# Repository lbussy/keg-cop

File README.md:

# Keg Cop

*Beverage Lines, Monitored.*

Keg Cop is an inexpensive and, most of all, simple to operate WiFi-enabled solution to maintain information about your Keezer, Kegerator, and Kegs.  Keg Cop enables you to use flowmeters of your choice (Swissflow during development) to monitor the contents of your kegs, and it even has a built-in Web UI to display what is on tap and how much is left.

Keg Cop uses an inexpensive ESP32 controller to control and monitor all aspects of your beverage dispensing solution.  If you already have flowmeters from another project, you can easily use those and upgrade your approach.  It will support one to nine flowmeters, and it will even control your temperatures for you.

You may employ up to five different temperature sensors to show you things like tower temp, keg temp, top and bottom of your Keezer, and you can even monitor the room temperature.

I designed this project as a complete system from the ground up.  Everything is provided, including board files for PCBs and 3D models for cases.  I’m releasing this system as something which provides either a complete recipe for success or enough information to allow you to roll your own if that’s your thing.

Whether you have one flowmeter or nine, Keg Cop can handle them.  Have more?  Add another controller, and KegScreen (coming soon!) will seamlessly display them all.

Want even more capabilities?  Keg Cop will report pours to Raspberry Pints via MQTT or a web endpoint with a generic JSON packet.
Still not enough?  Keg Cop was designed alongside KegScreen to work hand in hand with this exciting upcoming full-featured tap list solution.

Full documentation is provided, including the API and hardware assembly.  Or, if you are a more nuts and bolts person, GitHub may be the place for you!

Links and Support:

-	Home Page
-	Project on GitHub
-	Documentation
-	Report an Issue or Bug
-	Get support or chat with other users

This release has been a long time coming, and I’m excited to share this with you.  I want to thank the following folks from Homebrewtalk who have contributed in one way or another:

-	@thorrak
-	@gromitdj
-	@UncleD
-	@day_trippr
-	@cripplecreek

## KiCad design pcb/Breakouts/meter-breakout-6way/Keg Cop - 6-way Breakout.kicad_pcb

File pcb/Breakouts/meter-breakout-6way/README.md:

# Six-way Meter Breakout PCB

This PCB interfaces between the main Keg Cop board and up to six flow meters, which will connect via board-mounted JST-XH connectors.  This PCB is not designed to daisy-chain.

## Design info
This PCB was designed using [KiCad 6.0](https://www.kicad.org/), a free and open-source, cross-platform electronics design suite.  Design files are provided if you'd like to make changes to the design.  Otherwise, you can download the .zip file from the `Gerber` directory and upload to your PCB fab of choice.

## Board images
Front:

Back:

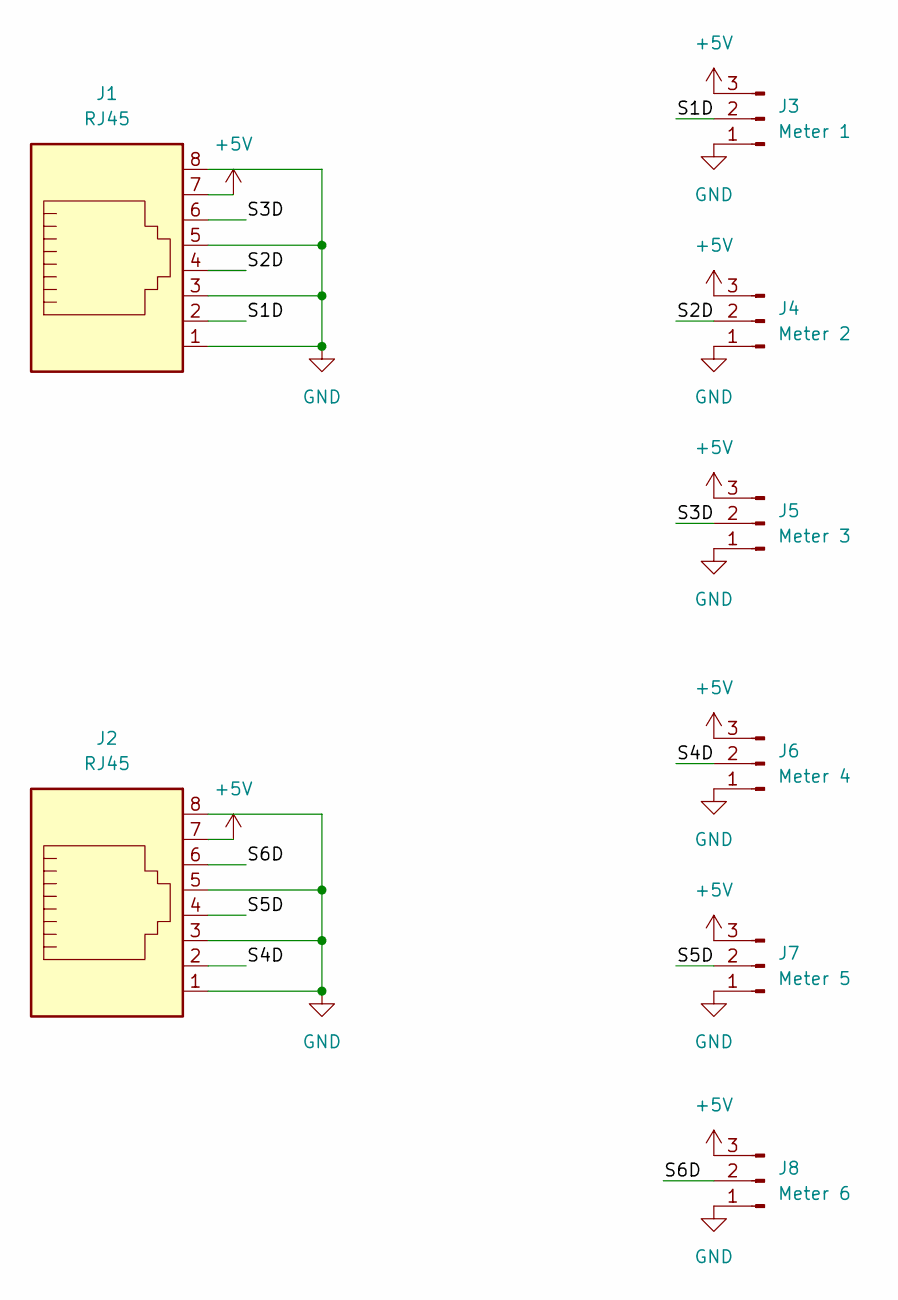
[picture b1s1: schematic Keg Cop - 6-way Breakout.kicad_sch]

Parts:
J1, J2: RJ45; RJ45_Amphenol_54602-x08_Horizontal
J3: Meter 1; JST_XH_B3B-XH-A_1x03_P2.50mm_Vertical
J4: Meter 2; JST_XH_B3B-XH-A_1x03_P2.50mm_Vertical
J5: Meter 3; JST_XH_B3B-XH-A_1x03_P2.50mm_Vertical
J6: Meter 4; JST_XH_B3B-XH-A_1x03_P2.50mm_Vertical
J7: Meter 5; JST_XH_B3B-XH-A_1x03_P2.50mm_Vertical
J8: Meter 6; JST_XH_B3B-XH-A_1x03_P2.50mm_Vertical

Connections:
+5V: J1.7, J2.7, J3.3, J4.3, J5.3, J6.3, J7.3, J8.3
/S1D: J1.2, J3.2
/S2D: J1.4, J4.2
/S3D: J1.6, J5.2
/S4D: J2.2, J6.2
/S5D: J2.4, J7.2
/S6D: J2.6, J8.2
GND: J1.1, J1.3, J1.5, J1.8, J2.1, J2.3, J2.5, J2.8, J3.1, J4.1, J5.1, J6.1, J7.1, J8.1

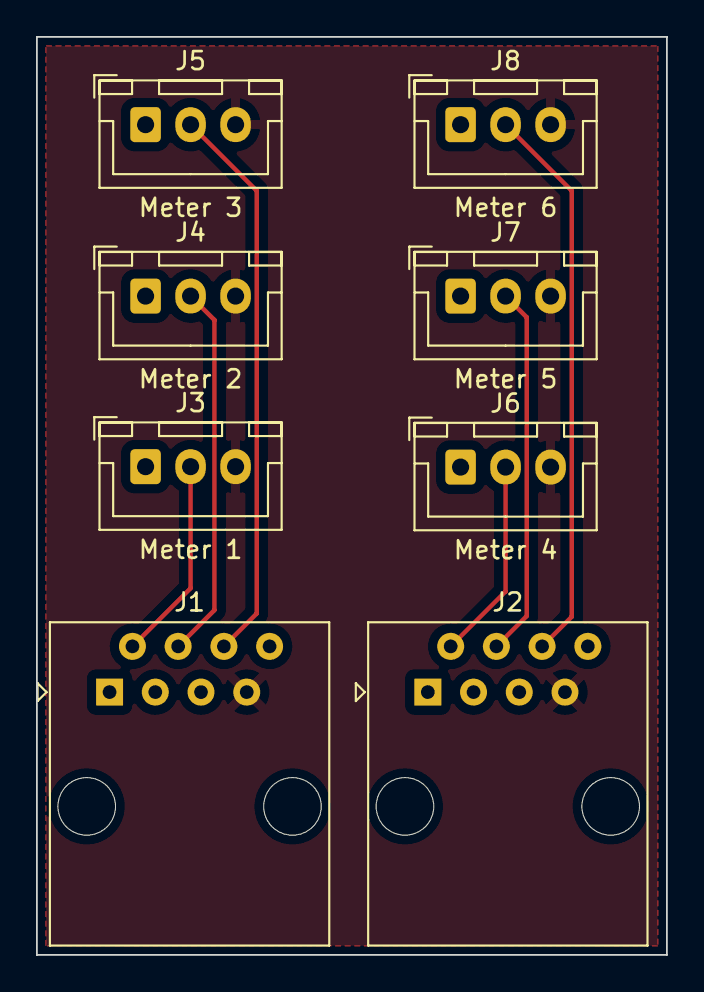
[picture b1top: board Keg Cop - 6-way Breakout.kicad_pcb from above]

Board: 2 copper layers, 35.0 x 51.0 mm, 8 parts (0 on the bottom side), 8 nets.

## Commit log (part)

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2022-09-05 Move JSON to stack
2022-09-05 Cleanup strings
2022-09-06 Move back to dynamic type
2022-09-07 Move common function to common file
2022-09-07 Allow builds outside of a repo
2022-09-07 Refactor API
2022-09-08 Add semaphores to prevent windup
2022-09-09 Use SPIFFS Editor
2022-09-09 Finish vestigial file management
2022-09-09 Fix API docs
2022-09-09 Fix API docs (#132)
2022-09-09 Move secret to a header (#133)
2022-09-09 Fix alert bars
2022-09-09 Fix alert bars (#134)
2022-09-09 Enable menu change on sensor change (#135)
2022-09-09 Version bump
2022-09-12 Update KSTV keys
2022-09-12 Remove debug condition on Telnet
2022-09-12 Cleanup debug (#136)
    * Add kstv.json
    * Update KSTV keys
    * Remove debug condition on Telnet
    * Remove debug condition on /edit
2022-09-12 Make keys public, add functions for KS-TV
2022-09-12 Remove needless keys, move KS-TV
2022-09-12 Fix a couple mistakes
2022-09-12 Kstv json (#137)
    * Add kstv.json
    * Update KSTV keys
    * Cleanup debug (#136)
    * Add kstv.json
    * Update KSTV keys
    * Remove debug condition on Telnet
2022-09-12 Don't need string
2022-09-12 Don't need string (#138)
2022-09-18 Move semaphore earlier
2022-09-18 Move reconnect out of callback
2022-09-18 Filesystem stability (#139)
    * Don't need string
    * Change to 5.0 class for SR-only
    * Move semaphore earlier
    * Move reconnect out of callback
    * Clean up filesystem logic
2022-09-18 Filesystem stability (#140)
    * Don't need string
    * Change to 5.0 class for SR-only
    * Move semaphore earlier
    * Move reconnect out of callback
    * Clean up filesystem logic
2022-09-18 Hide page when theme changes (#141)
2022-09-18 Update TODO
2022-09-21 Version update (#142)
2022-09-23 Remove kegscreen service advertisement
2022-09-25 Fix for #146
2023-04-07 Use proper div
2023-04-09 Go back to platform package 1.0.6
2023-04-11 Stub this in for later
2023-04-11 Explicit python decl
2023-04-11 Add .gz handler
2023-04-11 Update uptime refresh
2023-04-12 Ignore data
2023-04-12 I guess I don't need this
2023-04-12 Fix active links
2023-04-12 Fix fan control enabled assignment
2023-04-12 Fix for #152
2023-04-12 Fix for #149
2023-04-13 Version increment
2023-04-14 Restructure reconnect
2023-04-14 Restart serial and telnet
2023-04-14 Restart Web Server
2023-04-14 Reset main loop and filesystem
2023-04-14 Cleanup
2023-04-15 Cleanup logging
2023-04-15 Add some delays to allow Serial to start
2023-04-15 Lockout
2023-04-15 Separate stop and start
2023-04-15 Fix prefixes
2023-04-15 Loop logic
2023-04-15 Set autoconnect off
2023-04-15 Update Bootswatch
2023-04-15 Stub in hourly reboots
2023-04-15 Dis/reconnect on iter
2023-04-16 Reboot every 1 hour to avoid panic
2023-04-16 Logging cleanup
2023-04-16 Change to 2 hour reboot
2023-04-16 Standardize logic
2023-04-16 Tag new alpha
2023-04-18 Close FS after use
2023-04-19 Use single open/close
2023-04-19 Add delay to see startup Serial
2023-04-21 Fix John's 'feature'
2023-04-21 Refactor return
2023-04-22 Move theme to info
2023-04-23 Get rid of some harmless 404 erors
2023-04-23 Reset to 42 day reboot
2023-04-23 Add new file handler
2023-04-23 Fixed asynch error
2023-04-23 Update LCBUrl to HEAD
2023-04-23 Reverse order of debug
2023-04-23 Remove debug
2023-04-23 Change execution order
2023-04-25 Rearranged to allow flow load
2023-04-25 Nail down LCBUrl version
2023-04-29 Replace appconfig keys
2023-04-29 Add realm to authentication
2023-04-29 Stylize file buttons
2023-04-30 Add link to /fs/
2023-04-30 Style other buttons
2023-04-30 Exclude delete/download buttons
2023-04-30 Style/cancel upload
2023-05-11 Additional FS cleanup - stopping point
2023-05-11 Keep track of TODO
2023-05-11 Add debug
2023-05-11 Fix concatenation
2023-05-11 Add default TIO labels
2023-05-11 Fix label default
2023-05-11 Limit debug printing when file is missing
2023-05-11 Replace missing file
2023-05-11 Update version tag
2023-05-11 Realm is busted
2023-05-11 Restyle file list
2023-05-11 Disable/enable buttons
2023-05-11 Timeout messages
2023-05-11 Disable uploads
2023-05-13 Test uploads
2023-05-13 Rearrange events
2023-05-13 Pretty code
2023-05-13 Remive unused function
2023-05-13 Add secret to fs actions
2023-05-13 Add filename to prompt
2023-05-14 Restore file upload (#182)
    * Test uploads
    * Remove comments
    * Rearrange events
    * Pretty code
    * Remive unused function
    * Create new file upload
2023-05-14 Document fs page
2023-05-14 Remove /files/ from info
2023-05-14 Self-document fs API
2023-05-15 Split functions
2023-05-15 Document split fs api
2023-05-15 Fix file status display
2023-05-15 Update image
2023-05-15 Add fs api documentation
2023-05-15 Document fs (#183)
    * Document fs page
    * Self-document fs API
    * Fix file status display
    * Update image
    * Add fs api documentation
2023-05-15 Queue saves
2023-05-16 No longer used
2023-05-16 Use updated ArduinoJson
2023-05-16 Remove stupid workaround
2023-05-16 Add a better 404 handler
2023-05-16 Move to LittleFS
2023-05-16 Move license to md
2023-05-19 Littlefs (#186)
    * Move to LittleFS
    * Move license to md
2023-05-19 Avoid non reentrant code (#187)
2023-05-20 Fix viewport (#188)
2023-05-20 Rearrange fatal error
2023-05-20 Reset log priorities
2023-05-21 Add failure detect to app load
2023-05-21 Add debug to models
2023-05-21 Add handler for debug settings
2023-05-21 Add loglevel to serial init
2023-05-23 Add copy file function
2023-05-23 Leave notes
2023-05-23 Get rid of unneeded TODOs
2023-05-23 Use arguments for JSON load/save functions
2023-05-26 Update comments
2023-05-26 Leave myself a note
2023-05-29 Fix return
2023-05-29 Attempt config reload
2023-05-29 Backup config (#190)
    * Add failure detect to app load
    * Add copy file function
    * Handle LittleFS or SPIFFS
    * Use arguments for JSON load/save functions
    * Create backup after good file save
    * Fix return
2023-05-29 Backup config (#190)
    * Add failure detect to app load
    * Add copy file function
    * Handle LittleFS or SPIFFS
    * Use arguments for JSON load/save functions
    * Create backup after good file save
    * Fix return
2023-05-31 Update telnet lib
2023-05-31 Add telnet to web handler
2023-05-31 Add loglevel to web handler
2023-06-01 Add telnet and loglevel info
2023-06-01 Fix some scaling
2023-06-01 Change URL Target to Generic Rest
2023-06-01 Change URL Target to Generic Rest (#191)
2023-06-06 Bump version to Beta
2023-06-06 Fix docs requirements
2023-06-07 Handle LittleFS
2023-06-07 Add defaults
2023-06-07 Add back in async settings
2023-06-07 Restore saving theme
2023-06-07 Wrap debug settings in form
2023-06-07 Fix settings debug (#193)
    * Handle LittleFS
    * Fix debug line
    * Add defaults
    * Add back in async defines
    * Fix debug load
    * Restore saving theme
2023-06-08 Use explicit paths
2023-06-08 Reorder page handlers
2023-06-08 Fix routes
2023-06-08 Fs errors (#194)
    * Use explicit paths
    * Compress PNG too
    * Reorder page handlers
    * Fix routes
2023-06-08 Revert "Fs errors (#194)"
    This reverts commit 4d5f7bd300830cc77d4469af5861f50ff3dcb13e.
2023-06-08 Fs errors (#196)
    * Use explicit paths
    * Compress PNG too
    * Reorder page handlers
    * Fix routes
    * Turn off core debug
2023-06-08 Revert route changes
2023-06-08 Stub out nerw files
2023-06-08 New functions
2023-06-08 Start moving towards sync MQTT
2023-06-09 Remove RPints from setup
2023-06-09 Remove unused code
2023-06-09 Set up to use generic push
2023-06-09 No longer needed
2023-06-09 Move defines out of indiv headers
2023-06-09 Move wifihandler defines out of headers
2023-06-09 Move version defines out of headers
2023-06-09 Move urltarget defines out of headers
2023-06-09 Move uptimelog defines out of headers
2023-06-09 Move tools defines out of headers
2023-06-09 Move thermostat defines out of headers
2023-06-09 Move tempsensor defines out of headers
2023-06-09 Move taplistio defines out of headers
2023-06-09 Move resetreasons defines out of headers
2023-06-09 Move ntphandler defines out of headers
2023-06-09 Move main defines out of headers
2023-06-09 Move kegscreen defines out of headers
2023-06-09 Move flowconfig defines out of headers
2023-06-09 Move execota defines out of headers
2023-06-09 Move appconfig defines out of headers
2023-06-09 Protect Includes & Defines (#197)
    * Move defines out of indiv headers
    * Move wifihandler includes out of headers
    * Move webpagehandler includes out of headers
    * Move version includes out of headers
    * Move urltarget includes out of headers
    * Move uptimelog includes out of headers
2023-06-10 New RPints push
2023-06-10 Get rid of old notes
2023-06-10 Address templating and push logic
2023-06-10 Fix RPints template
2023-06-10 Fix pulse reports
2023-06-10 RPints push finished
2023-06-10 Switch MQTT Libs (#198)
    * Go back to a normal MQTT lib
    * Remove RPints from setup
    * Set up to use generic push
    * Protect Includes & Defines (#197)
    * New RPints push
    * Address templating and push logic
2023-06-11 Clean up logging
2023-06-11 Add HA config to settings
2023-06-11 Add Mosquitto setup steps to troubleshooting
2023-06-11 Update documentation for HA context
2023-06-11 Handle HA config post
2023-06-11 Add HA files
2023-06-12 Rough out functions
2023-06-16 Change field to password
2023-06-16 Initial device discovery
2023-06-16 Normalize abbrev
2023-06-20 Working templates
2023-06-21 Change log level
2023-06-21 Re-use portions of template
2023-06-21 Fix status for binaries
2023-06-21 Send only when enabled
2023-06-23 Initial HASS push on startup
2023-06-24 Remove spam
2023-06-24 Add in state changes
2023-06-25 Change default logging
2023-06-25 Queue HASS functions
2023-06-25 Queuing and availability
2023-06-25 GEt rid of vestigal JSON code
2023-06-25 Update MQTT documentation
2023-06-25 Use initial and ongoing timer for HASS
2023-06-25 Get rid of compiler warning
2023-06-25 Reduce logging level
2023-06-26 Add single point re-broadcast
2023-06-26 Fix solenoid state
2023-06-26 Fixed logic
2023-06-26 MQTT update for only selected sensor
2023-06-26 MQTT update for unavailable too
2023-06-26 Make change on tap post
2023-06-26 Reset control state on sensor unavail
2023-06-30 Disable CP when sensor is disabled
2023-06-30 Home asst (#199)
    * Switch MQTT Libs (#198)
    * Set up to use generic push
    * Protect Includes & Defines (#197)
    * New RPints push
    * Address templating and push logic
    * Get rid of 24hr timer
2023-07-08 Add kickdetect to web settings
2023-07-08 Add kickdetect to settings
2023-07-08 Allow skipping kickdetect
2023-07-08 Change verbiage
2023-07-08 Config kick detect (#200)
    * Update TODO
    * Add kickdetect to model
    * Add kickdetect to web settings
    * Add kickdetect to settings
    * Add kickdetect to API
    * Allow skipping kickdetect
2023-07-16 Allow a reconect
2023-07-16 Fix temp page control link
2023-07-19 Bunp version
2023-07-19 Feature Release 1.3.0 (#202)
    * Remove kegscreen service advertisement
    * Fix mDNS keys
    * Fix for #146
    * Use proper div
    * Add scanNetworks() to reconnect
    * Go back to platform package 1.0.6
2023-07-28 Document Home Assistant integration (#203)
2023-08-16 Update readthedocs.yaml
    The `build.image` config key on `.readthedocs.yaml` has been deprecated, and will be removed on October 16, 2023.
2023-08-16 Rename images
2023-08-16 Devel doc (#204)
    * Document Home Assistant integration (#203)
    * Update readthedocs.yaml
    The `build.image` config key on `.readthedocs.yaml` has been deprecated, and will be removed on October 16, 2023.
    * Rename images
    * Run through grammarly
    ---------
2023-08-16 Devel doc (#205)
    * Document Home Assistant integration (#203)
    * Update readthedocs.yaml
    The `build.image` config key on `.readthedocs.yaml` has been deprecated, and will be removed on October 16, 2023.
    * Rename images
    * Run through grammarly
    * Need py <= 3.8
2023-08-16 Still hammering on readthedocs
2023-08-16 Devel doc (#207)
    * Document Home Assistant integration (#203)
    * Update readthedocs.yaml
    The `build.image` config key on `.readthedocs.yaml` has been deprecated, and will be removed on October 16, 2023.
    * Rename images
    * Run through grammarly
    * Need py <= 3.8
2023-08-16 Integrate HASS Customization
2023-08-16 Devel doc (#208)
    * Document Home Assistant integration (#203)
    * Update readthedocs.yaml
    The `build.image` config key on `.readthedocs.yaml` has been deprecated, and will be removed on October 16, 2023.
    * Rename images
    * Run through Grammarly
    * Need py == 3.10
